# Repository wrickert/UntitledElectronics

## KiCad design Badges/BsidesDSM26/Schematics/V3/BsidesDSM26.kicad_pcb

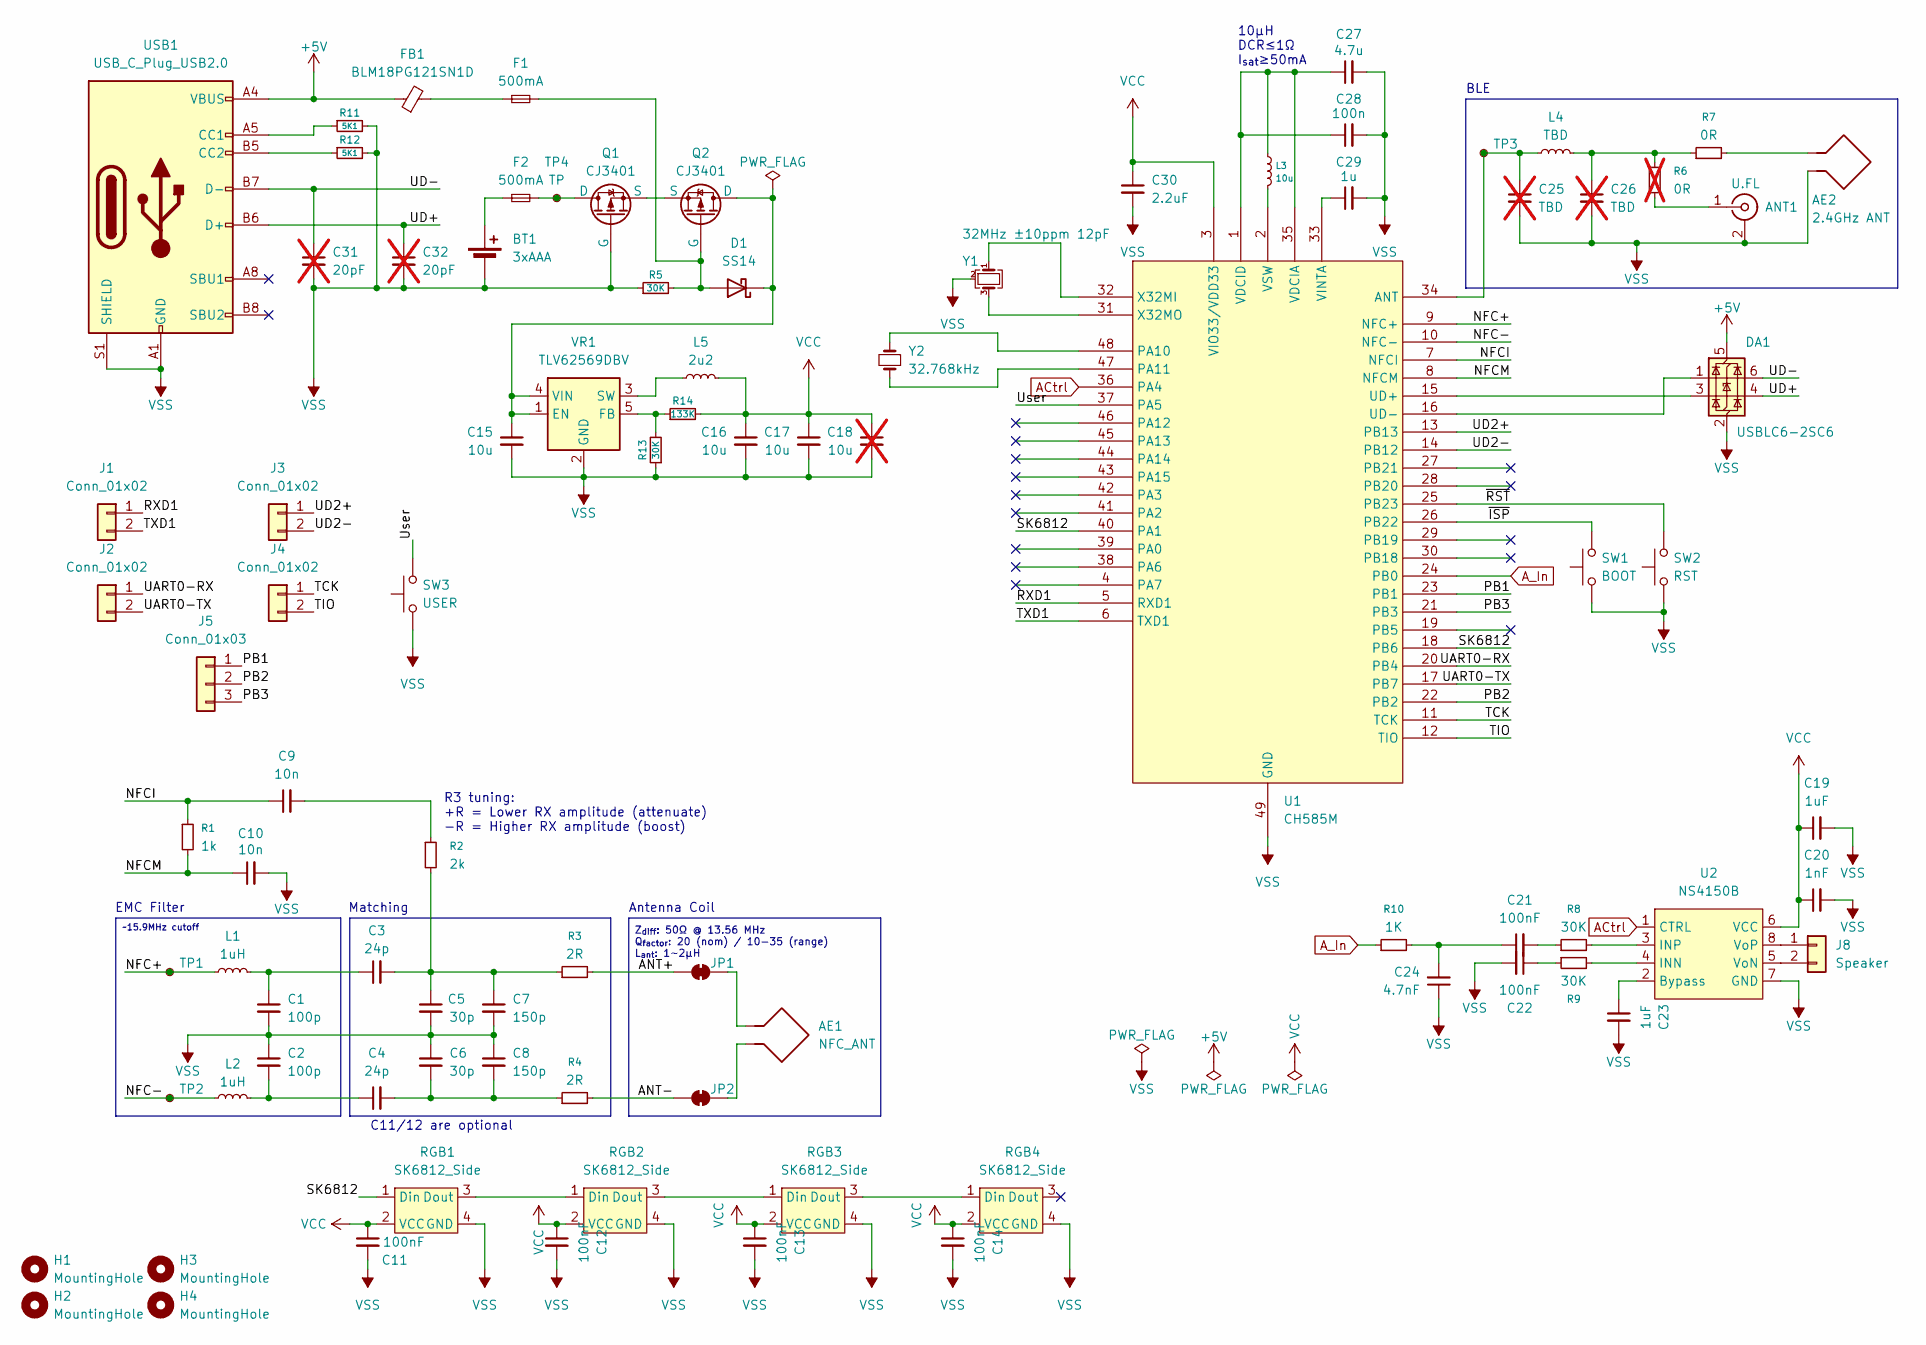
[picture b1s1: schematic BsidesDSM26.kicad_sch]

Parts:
AE1: NFC_ANT; NFC Anenna
AE2: 2.4GHz ANT; Texas_SWRA117D_2.4GHz_Left
ANT1: U.FL; U.FL_Hirose_U.FL-R-SMT-1_Vertical
BT1: 3xAAA; Keystone_5226_3AAA
C1, C2: 100p; C_0603_1608Metric
C3, C4: 24p; C_0603_1608Metric
C5, C6: 30p; C_0603_1608Metric
C7, C8: 150p; C_0603_1608Metric
C9, C10: 10n; C_0603_1608Metric
C11, C12, C13, C14, C21, C22: 100nF; C_0805_2012Metric
C15, C16, C17: 10u; C_0603_1608Metric; LCSC C3039688
C18: 10u; C_0603_1608Metric; LCSC C3039688; not fitted
C19: 1uF; C_0603_1608Metric
C20: 1nF; C_0603_1608Metric
C23: 1uF; C_0805_2012Metric
C24: 4.7nF; C_0805_2012Metric
C25, C26: TBD; C_0603_1608Metric; not fitted
C27: 4.7u; C_0603_1608Metric
C28: 100n; C_0805_2012Metric
C29: 1u; C_0603_1608Metric
C30: 2.2uF; C_0603_1608Metric
C31, C32: 20pF; C_0402_1005Metric_Pad0.74x0.62mm_HandSolder; not fitted
D1: SS14; D_SMA; LCSC C2986110
DA1: USBLC6-2SC6; SOT-23-6
F1, F2: 500mA; Fuse_1206_3216Metric; LCSC C2680506
FB1: BLM18PG121SN1D; L_0603_1608Metric_Pad1.05x0.95mm_HandSolder; LCSC C14709
H1, H2, H3, H4: MountingHole; M3ThreadedStandoff
J1, J2, J3, J4: Conn_01x02; PinHeader_1x02_P1.00mm_Vertical
J5: Conn_01x03; PinHeader_1x03_P2.54mm_Vertical
J8: Speaker; Molex_PicoBlade_53261-0271_1x02-1MP_P1.25mm_Horizontal
JP1, JP2: SolderJumper_2_Bridged; SolderJumper-2_P1.3mm_Bridged_RoundedPad1.0x1.5mm
L1, L2: 1uH; L_0603_1608Metric
L3: 10u; L_1008_2520Metric
L4: TBD; L_0603_1608Metric
L5: 2u2; L_1008_2520Metric_Pad1.43x2.20mm_HandSolder; LCSC C206332
Q1, Q2: CJ3401; SOT-23; LCSC C13799
R1: 1k; R_0603_1608Metric
R2: 2k; R_0603_1608Metric
R3, R4: 2R; R_0603_1608Metric
R5, R8, R9: 30K; R_0805_2012Metric
R6: 0R; R_0603_1608Metric; not fitted
R7: 0R; R_0603_1608Metric
R10: 1K; R_0805_2012Metric
R11, R12: 5K1; R_0603_1608Metric
R13: 30K; R_0603_1608Metric
R14: 133K; R_0603_1608Metric
RGB1, RGB2, RGB3, RGB4: SK6812_Side; SK6812SIDE-A-RVS
SW1: BOOT; TS3315A
SW2: RST; TS3315A
SW3: USER; TS3315A
TP1, TP2, TP3: TestPoint_Small; TestPoint_Pad_D1.0mm
TP4: TP; TestPoint_Pad_D1.0mm
U1: CH585M; QFN-48-1EP_5x5mm_P0.35mm_EP3.7x3.7mm
U2: NS4150B; MSOP-8_3x3mm_P0.65mm
USB1: USB_C_Plug_USB2.0; USB_C_Receptical-Jing
VR1: TLV62569DBV; SOT-23-5; LCSC C141836
Y1: 32MHz ±10ppm 12pF; Crystal_SMD_3225-4Pin_3.2x2.5mm
Y2: 32.768kHz; Crystal_SMD_3215-2Pin_3.2x1.5mm

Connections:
+5V: DA1.5 (VBUS), FB1.1, USB1.A4 (VBUS), USB1.A9 (VBUS), USB1.B4 (VBUS), USB1.B9 (VBUS)
/ANT+: JP1.1 (A), R3.2
/ANT-: JP2.1 (A), R4.2
/NFC+: L1.1, TP1.1 (1_1), U1.9 (NFC+)
/NFC-: L2.1, TP2.1 (1_1), U1.10 (NFC-)
/NFCI: C9.1, R1.1, U1.7 (NFCI)
/NFCM: C10.1, R1.2, U1.8 (NFCM)
/PB1: J5.1, U1.23 (PB1)
/PB2: J5.2, U1.22 (PB2)
/PB3: J5.3, U1.21 (PB3)
/RXD1: J1.1, U1.5 (RXD1)
/SK6812: RGB1.1 (Din), U1.18 (PB6), U1.40 (PA1)
/TCK: J4.1, U1.11 (TCK)
/TIO: J4.2, U1.12 (TIO)
/TXD1: J1.2, U1.6 (TXD1)
/UART0-RX: J2.1, U1.20 (PB4)
/UART0-TX: J2.2, U1.17 (PB7)
/UD2+: J3.1, U1.13 (PB13)
/UD2-: J3.2, U1.14 (PB12)
/UD+: C32.1, DA1.4 (I/O2), USB1.A6 (D+), USB1.B6 (D+)
/UD-: C31.1, DA1.6 (I/O1), USB1.A7 (D-), USB1.B7 (D-)
/User: SW3.2, U1.37 (PA5)
/~ISP: SW1.2, U1.26 (PB22)
/~RST: SW2.2, U1.25 (PB23)
ACtrl: U1.36 (PA4), U2.1 (CTRL)
A_In: R10.1, U1.24 (PB0)
unnamed: AE2.1, R7.2
unnamed: ANT1.1 (In), R6.2
unnamed: BT1.1 (+), F2.1
unnamed: C1.1, C3.1, L1.2
unnamed: C2.2, C4.1, L2.2
unnamed: C3.2, C5.1, C7.1, R2.2, R3.1
unnamed: C4.2, C6.2, C8.2, R4.1
unnamed: C9.2, R2.1
unnamed: C21.1, C24.2, R10.2
unnamed: C21.2, R8.1
unnamed: C22.1, R9.1
unnamed: C26.1, L4.2, R6.1, R7.1
unnamed: D1.2 (A), F1.2, Q2.1 (G), R5.2
unnamed: C15.1, D1.1 (K), Q2.3 (D), VR1.1 (EN), VR1.4 (VIN)
unnamed: F1.1, FB1.2
unnamed: J8.1, U2.8 (VoP)
unnamed: J8.2, U2.5 (VoN)
unnamed: AE1.1, JP1.2 (B)
unnamed: AE1.2, JP2.2 (B)
unnamed: F2.2, Q1.3 (D), TP4.1 (1_1)
unnamed: Q1.2 (S), Q2.2 (S)
unnamed: RGB1.3 (Dout), RGB2.1 (Din)
unnamed: RGB2.3 (Dout), RGB3.1 (Din)
unnamed: RGB3.3 (Dout), RGB4.1 (Din)
unnamed: C25.1, L4.1, TP3.1 (1_1), U1.34 (ANT)
unnamed: U1.48 (PA10), Y2.2
unnamed: U1.47 (PA11), Y2.1
unnamed: DA1.1 (I/O1), U1.16 (UD-)
unnamed: DA1.3 (I/O2), U1.15 (UD+)
unnamed: C27.1, C28.1, L3.1, U1.1 (VDCID), U1.35 (VDCIA)
unnamed: C29.1, U1.33 (VINTA)
unnamed: L3.2, U1.2 (VSW)
unnamed: U1.32 (X32MI), Y1.1
unnamed: U1.31 (X32MO), Y1.3
unnamed: C23.1, U2.2 (Bypass)
unnamed: R9.2, U2.4 (INN)
unnamed: R8.2, U2.3 (INP)
unnamed: R11.1, USB1.A5 (CC1)
unnamed: R12.1, USB1.B5 (CC2)
unnamed: R13.2, R14.1, VR1.5 (FB)
unnamed: L5.1, VR1.3 (SW)
VCC: C11.1, C12.1, C13.1, C14.1, C16.1, C17.1, C18.1, C19.1, C20.1, C30.1, L5.2, R14.2, RGB1.2 (VCC), RGB2.2 (VCC), RGB3.2 (VCC), RGB4.2 (VCC), U1.3 (VIO33/VDD33), U2.6 (VCC)
VSS: AE2.2, ANT1.2 (Ext), BT1.2 (-), C1.2, C2.1, C5.2, C6.1, C7.2, C8.1, C10.2, C11.2, C12.2, C13.2, C14.2, C15.2, C16.2, C17.2, C18.2, C19.2, C20.2, C22.2, C23.2, C24.1, C25.2, C26.2, C27.2, C28.2, C29.2, C30.2, C31.2, C32.2, DA1.2 (GND), Q1.1 (G), R5.1, R11.2, R12.2, R13.1, RGB1.4 (GND), RGB2.4 (GND), RGB3.4 (GND), RGB4.4 (GND), SW1.1, SW2.1, SW3.1, U1.49 (GND), U2.7 (GND), USB1.A1 (GND), USB1.A12 (GND), USB1.B1 (GND), USB1.B12 (GND), USB1.S1 (SHIELD), VR1.2 (GND), Y1.2 (G), Y1.4 (G)

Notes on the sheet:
10µH DCR≤1Ω I_{sat}≥50mA
Antenna Coil
Matching
Z_{diff​}: 50Ω @ 13.56 MHz Q_{factor​}: 20 (nom) / 10-35 (range) L_{ant​}: 1∼2μH
BLE
C11/12 are optional
EMC Filter
~15.9MHz cutoff
R3 tuning: +R = Lower RX amplitude (attenuate) -R = Higher RX amplitude (boost)

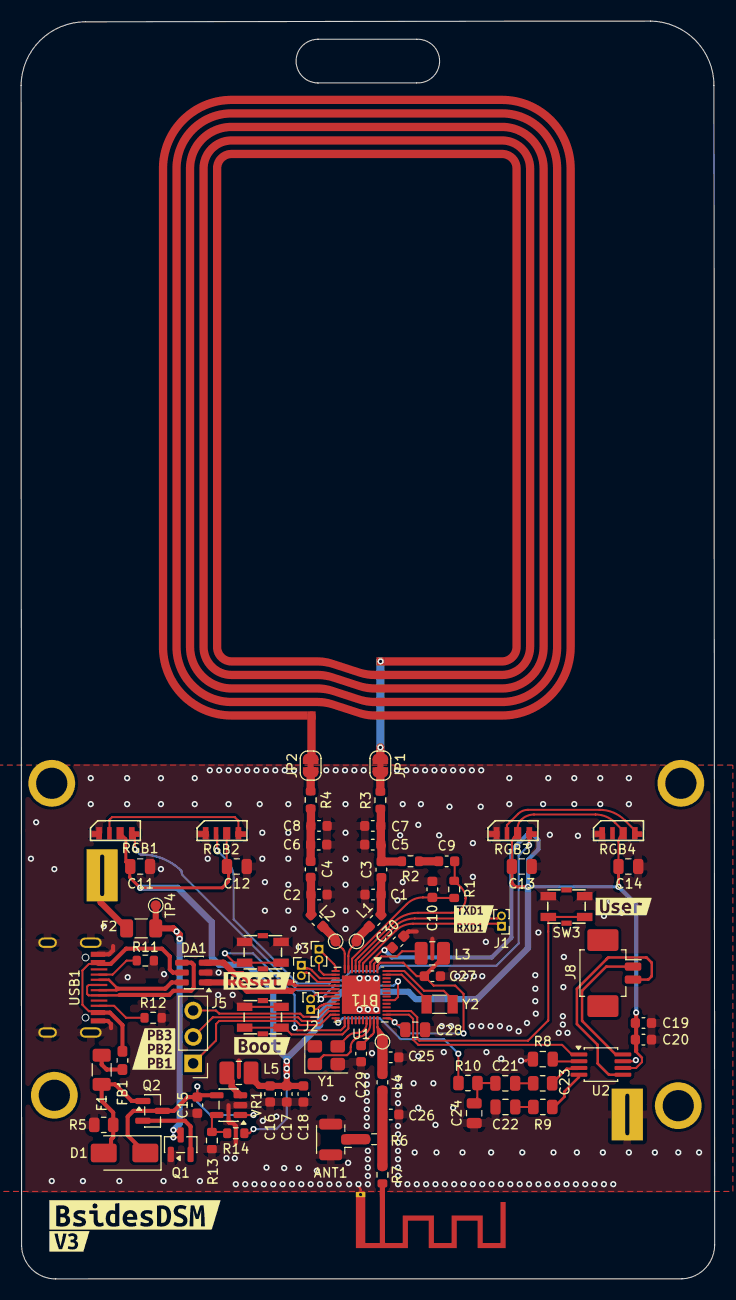
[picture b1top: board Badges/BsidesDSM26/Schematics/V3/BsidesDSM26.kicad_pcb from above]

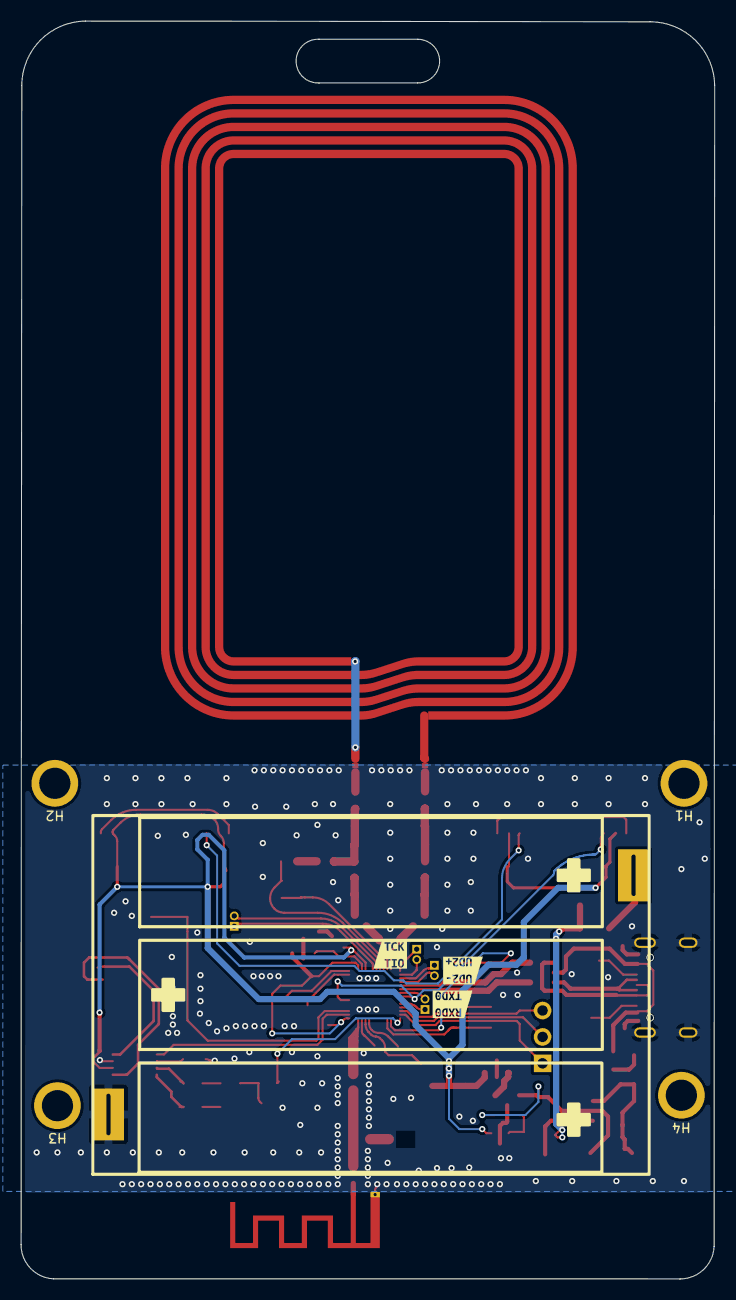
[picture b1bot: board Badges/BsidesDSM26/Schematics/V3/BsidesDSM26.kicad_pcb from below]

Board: 2 copper layers, 66.7 x 121.0 mm, 99 parts (7 on the bottom side), 69 nets.

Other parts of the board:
kibuzzard-6A035753: G***; kibuzzard-6A035753
kibuzzard-69CD6EDC: G***; kibuzzard-69CD6EDC
kibuzzard-69CD7A0E: G***; kibuzzard-69CD7A0E
kibuzzard-69CD7A3A: G***; kibuzzard-69CD7A3A
kibuzzard-69CD78FD: G***; kibuzzard-69CD78FD
kibuzzard-69CD79CB: G***; kibuzzard-69CD79CB
kibuzzard-69CD792A: G***; kibuzzard-69CD792A
kibuzzard-69CD7907: G***; kibuzzard-69CD7907
kibuzzard-69CD7919: G***; kibuzzard-69CD7919
kibuzzard-69FCE3C1: G***; kibuzzard-69FCE3C1

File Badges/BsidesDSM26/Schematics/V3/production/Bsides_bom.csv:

Designator,Footprint,Quantity,Value,LCSC Part #,Production
AE1,NFC Anenna,1,NFC_ANT,DNP,
AE2,Texas_SWRA117D_2.4GHz_Left,1,2.4GHz ANT,DNP,
ANT1,U.FL_Hirose_U.FL-R-SMT-1_Vertical,1,U.FL,DNP,
BT1,Keystone_5226_3AAA,1,3xAAA,DNP,
"C1, C2",603,2,100p,C576835,
"C10, C9",603,2,10n,C57112,
"C11, C12, C13, C14, C21, C22",805,6,100nF,C49678,
"C15, C16, C17, C18",603,4,10u,C3039688,
C19,603,1,1uF,C15849,
C20,603,1,1nF,C57112,
C23,805,1,1uF,C28323,
C24,805,1,4.7nF,C1779,
"C25, C26, L4",603,3,TBD,DNP,
C27,603,1,4.7u,C19666,
C28,805,1,100n,C49678,
C29,603,1,1u,C15849,
"C3, C4",603,2,24p,C107044,
C30,603,1,2.2uF,C23630,
"C31, C32",402,2,20pF,DNP,
"C5, C6",603,2,30p,C1658,
"C7, C8",603,2,150p,C22399613,
D1,D_SMA,1,SS14,C2986110,
DA1,SOT-23-6,1,USBLC6-2SC6,C7519,
"F1, F2",1206,2,500mA,C2680506,
FB1,603,1,BLM18PG121SN1D,C14709,
"J1, J2, J3, J4",PinHeader_1x02_P1.00mm_Vertical,4,Conn_01x02,DNP,
J5,PinHeader_1x03_P2.54mm_Vertical,1,Conn_01x03,DNP,
J8,Molex_PicoBlade_53261-0271_1x02-1MP_P1.25mm_Horizontal,1,Speaker,C7433453,
"L1, L2",603,2,1uH,C711163,
L3,1008,1,10u,C5289273 ,
L5,1008,1,2u2,C206332,
"Q1, Q2",SOT-23,2,CJ3401,C13799,
R1,603,1,1k,C21190,
R10,805,1,1K,C17513,
"R11, R12",603,2,5K1,C23186,
R13,603,1,30K,C22984,
R14,603,1,133K,C861659,
R2,603,1,2k,C22975,
"R3, R4",603,2,2R,C22977,
"R5, R8, R9",805,3,30K,C17621,
"R6, R7",603,2,0R,DNP,
"RGB1, RGB2, RGB3, RGB4",SK6812SIDE-A-RVS,4,SK6812_Side,C5378737,
SW1,TS3315A,1,BOOT,C2905041,
SW2,TS3315A,1,RST,C2905041,
SW3,TS3315A,1,USER,C2905041,
"TP1, TP2, TP3",TestPoint_Pad_D1.0mm,3,TestPoint_Small,DNP,
TP4,TestPoint_Pad_D1.0mm,1,TP,DNP,
U1,QFN-48-1EP_5x5mm_P0.35mm_EP3.7x3.7mm,1,CH585M,C42381469,
U2,MSOP-8_3x3mm_P0.65mm,1,NS4150B,C189961,
USB1,USB_C_Receptical-Jing,1,USB_C_Plug_USB2.0,C47345355,
VR1,SOT-23-5,1,TLV62569DBV,C141836,
Y1,Crystal_SMD_3225-4Pin_3.2x2.5mm,1,32MHz ±10ppm 12pF,C19723366,
Y2,Crystal_SMD_3215-2Pin_3.2x1.5mm,1,32.768kHz,C32346,

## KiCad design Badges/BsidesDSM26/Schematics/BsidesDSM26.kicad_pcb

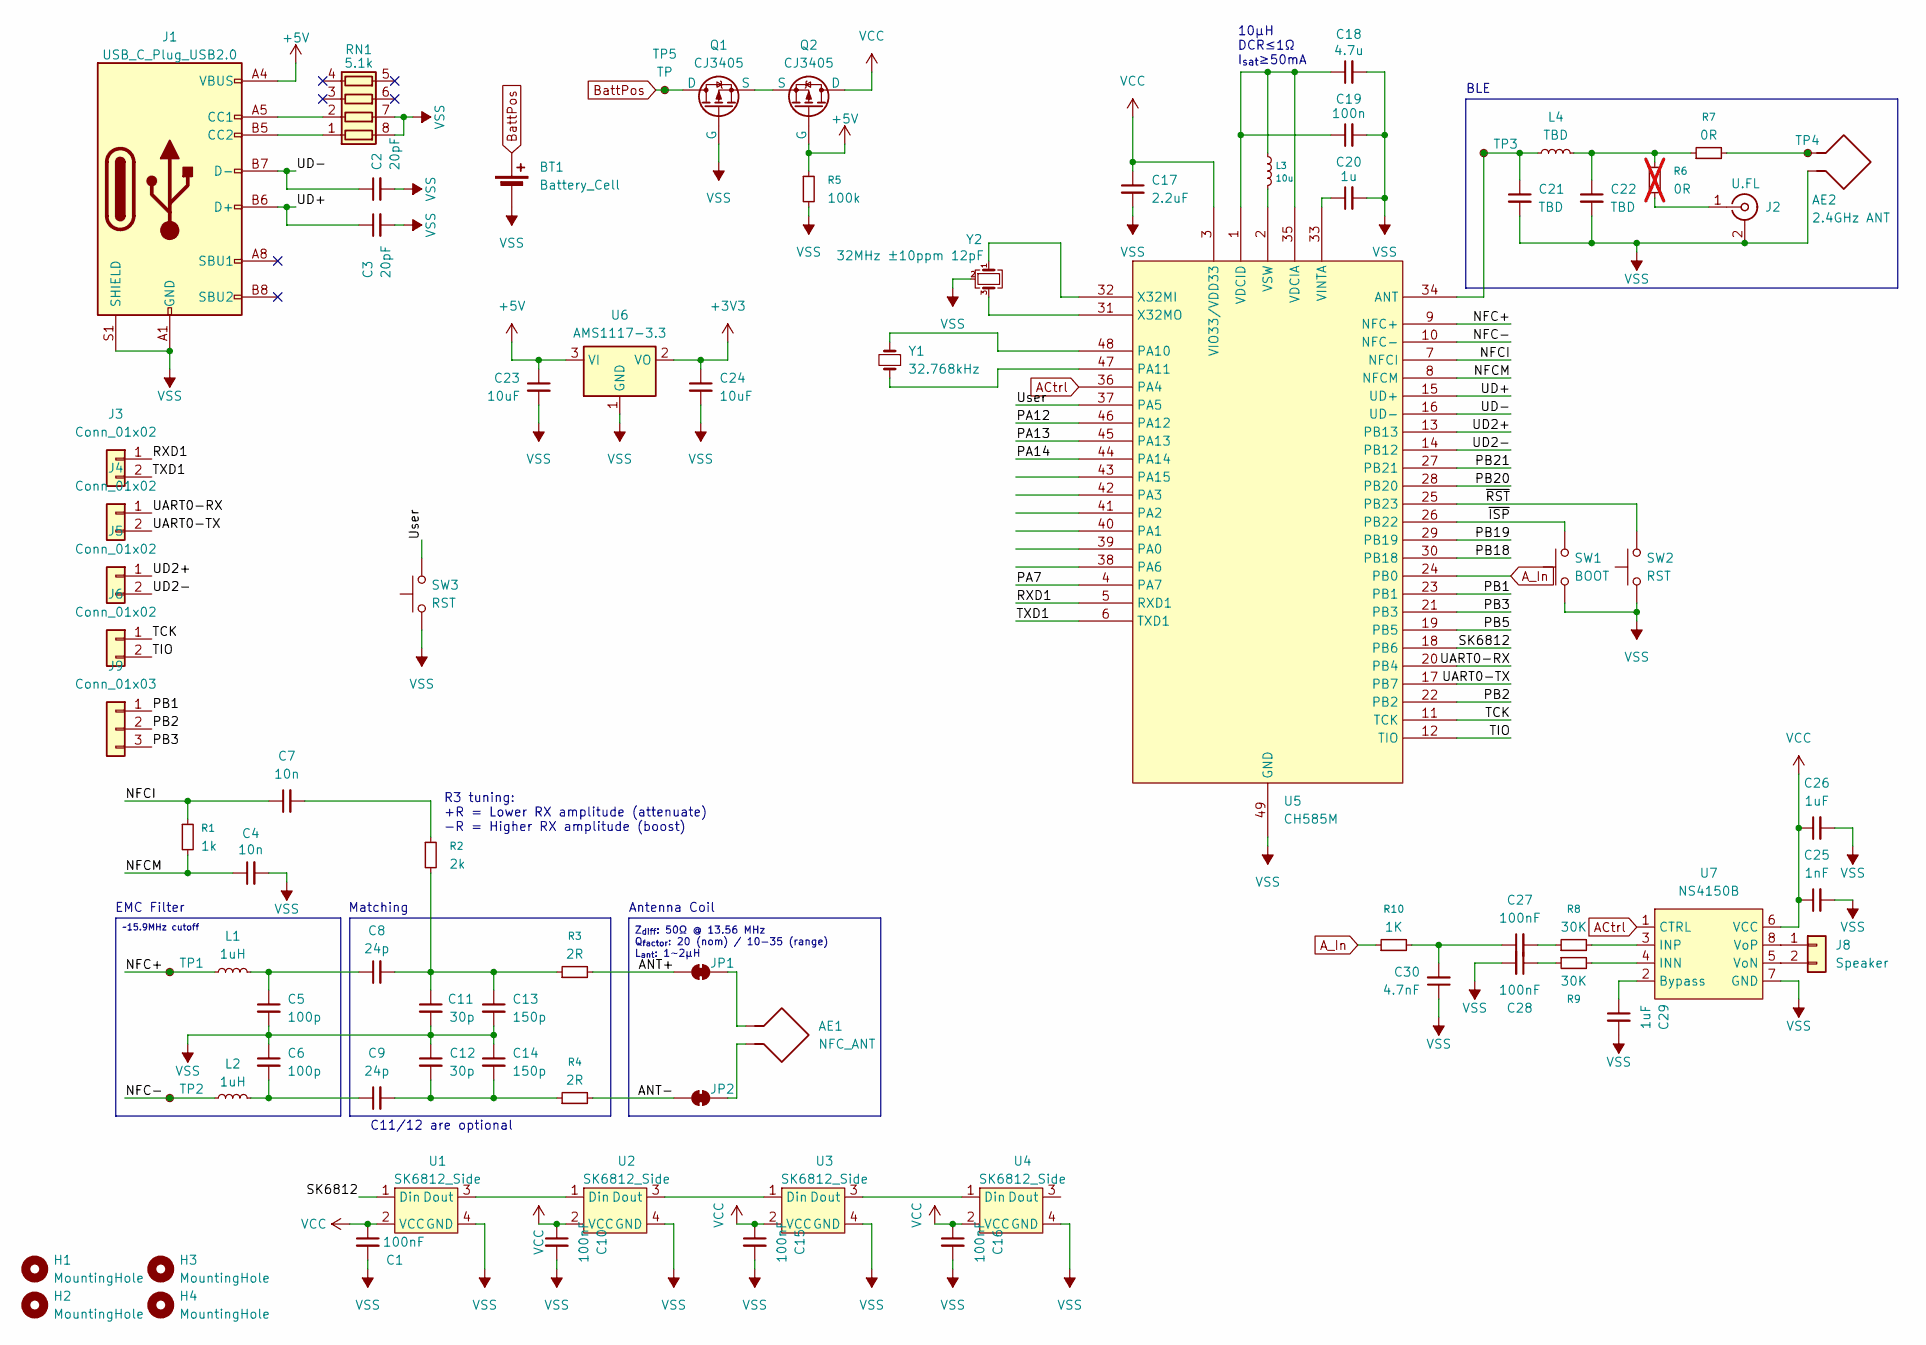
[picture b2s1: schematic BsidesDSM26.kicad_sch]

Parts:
AE1: NFC_ANT; NFC Anenna
AE2: 2.4GHz ANT; Texas_SWRA117D_2.4GHz_Left
BT1: Battery_Cell; Keystone5220_AA
C1, C10, C15, C16, C27, C28: 100nF; C_0805_2012Metric
C2, C3: 20pF; C_0805_2012Metric
C4, C7: 10n; C_0603_1608Metric
C5, C6: 100p; C_0603_1608Metric
C8, C9: 24p; C_0603_1608Metric
C11, C12: 30p; C_0603_1608Metric
C13, C14: 150p; C_0603_1608Metric
C17: 2.2uF; C_0805_2012Metric
C18: 4.7u; C_0805_2012Metric
C19: 100n; C_0603_1608Metric
C20: 1u; C_0603_1608Metric
C21, C22: TBD; C_0603_1608Metric
C23, C24: 10uF; C_0805_2012Metric
C25: 1nF; C_0805_2012Metric
C26, C29: 1uF; C_0805_2012Metric
C30: 4.7nF; C_0805_2012Metric
H1, H2, H3, H4: MountingHole; M3ThreadedStandoff
J1: USB_C_Plug_USB2.0; USB_C_Receptical-Jing
J2: U.FL; U.FL_Hirose_U.FL-R-SMT-1_Vertical
J3, J4, J5, J6: Conn_01x02; PinHeader_1x02_P1.00mm_Vertical
J8: Speaker; Molex_PicoBlade_53261-0271_1x02-1MP_P1.25mm_Horizontal
J9: Conn_01x03; PinHeader_1x03_P2.54mm_Vertical
JP1, JP2: SolderJumper_2_Bridged; SolderJumper-2_P1.3mm_Bridged_RoundedPad1.0x1.5mm
L1, L2: 1uH; L_0603_1608Metric
L3: 10u; L_1008_2520Metric
L4: TBD; L_0603_1608Metric
Q1, Q2: CJ3405; SOT-23
R1: 1k; R_0603_1608Metric
R2: 2k; R_0603_1608Metric
R3, R4: 2R; R_0603_1608Metric
R5: 100k; R_0805_2012Metric
R6: 0R; R_0603_1608Metric; not fitted
R7: 0R; R_0603_1608Metric
R8, R9: 30K; R_0805_2012Metric
R10: 1K; R_0805_2012Metric
RN1: 5.1k; R_Array_Convex_4x0603
SW1: BOOT; TS3315A
SW2, SW3: RST; TS3315A
TP1, TP2, TP3, TP4: TestPoint_Small; TestPoint_Pad_D1.0mm
TP5: TP; TestPoint_Pad_D1.0mm
U1, U2, U3, U4: SK6812_Side; SK6812SIDE-A-RVS
U5: CH585M; QFN-48-1EP_5x5mm_P0.35mm_EP3.7x3.7mm
U6: AMS1117-3.3; SOT-223-3_TabPin2
U7: NS4150B; MSOP-8_3x3mm_P0.65mm
Y1: 32.768kHz; Crystal_SMD_3215-2Pin_3.2x1.5mm
Y2: 32MHz ±10ppm 12pF; Crystal_SMD_3225-4Pin_3.2x2.5mm

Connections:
+5V: C23.1, J1.A4 (VBUS), J1.A9 (VBUS), J1.B4 (VBUS), J1.B9 (VBUS), Q2.1 (G), R5.1, U6.3 (VI)
/ANT+: JP1.1 (A), R3.2
/ANT-: JP2.1 (A), R4.2
/NFC+: L1.1, TP1.1, U5.9 (NFC+)
/NFC-: L2.1, TP2.1, U5.10 (NFC-)
/NFCI: C7.1, R1.1, U5.7 (NFCI)
/NFCM: C4.1, R1.2, U5.8 (NFCM)
/PA7: U5.4 (PA7)
/PA12: U5.46 (PA12)
/PA13: U5.45 (PA13)
/PA14: U5.44 (PA14)
/PB1: J9.1, U5.23 (PB1)
/PB2: J9.2, U5.22 (PB2)
/PB3: J9.3, U5.21 (PB3)
/PB5: U5.19 (PB5)
/PB18: U5.30 (PB18)
/PB19: U5.29 (PB19)
/PB20: U5.28 (PB20)
/PB21: U5.27 (PB21)
/RXD1: J3.1, U5.5 (RXD1)
/SK6812: U1.1 (Din), U5.18 (PB6)
/TCK: J6.1, U5.11 (TCK)
/TIO: J6.2, U5.12 (TIO)
/TXD1: J3.2, U5.6 (TXD1)
/UART0-RX: J4.1, U5.20 (PB4)
/UART0-TX: J4.2, U5.17 (PB7)
/UD2+: J5.1, U5.13 (PB13)
/UD2-: J5.2, U5.14 (PB12)
/UD+: C3.1, J1.A6 (D+), J1.B6 (D+), U5.15 (UD+)
/UD-: C2.1, J1.A7 (D-), J1.B7 (D-), U5.16 (UD-)
/User: SW3.2, U5.37 (PA5)
/~ISP: SW1.2, U5.26 (PB22)
/~RST: SW2.2, U5.25 (PB23)
ACtrl: U5.36 (PA4), U7.1 (CTRL)
A_In: R10.1, U5.24 (PB0)
BattPos: BT1.1 (+), Q1.3 (D), TP5.1
unnamed: AE2.1, R7.2, TP4.1
unnamed: C5.1, C8.1, L1.2
unnamed: C6.2, C9.1, L2.2
unnamed: C7.2, R2.1
unnamed: C8.2, C11.1, C13.1, R2.2, R3.1
unnamed: C9.2, C12.2, C14.2, R4.1
unnamed: C22.1, L4.2, R6.1, R7.1
unnamed: C27.1, C30.2, R10.2
unnamed: C27.2, R8.1
unnamed: C28.1, R9.1
unnamed: J1.A5 (CC1), RN1.2 (R2.1)
unnamed: J1.B5 (CC2), RN1.1 (R1.1)
unnamed: J2.1 (In), R6.2
unnamed: J8.1, U7.8 (VoP)
unnamed: J8.2, U7.5 (VoN)
unnamed: AE1.1, JP1.2 (B)
unnamed: AE1.2, JP2.2 (B)
unnamed: Q1.2 (S), Q2.2 (S)
unnamed: U1.3 (Dout), U2.1 (Din)
unnamed: U2.3 (Dout), U3.1 (Din)
unnamed: U3.3 (Dout), U4.1 (Din)
unnamed: C21.1, L4.1, TP3.1, U5.34 (ANT)
unnamed: U5.48 (PA10), Y1.2
unnamed: U5.47 (PA11), Y1.1
unnamed: C18.1, C19.1, L3.1, U5.1 (VDCID), U5.35 (VDCIA)
unnamed: C20.1, U5.33 (VINTA)
unnamed: L3.2, U5.2 (VSW)
unnamed: U5.32 (X32MI), Y2.1
unnamed: U5.31 (X32MO), Y2.3
unnamed: C29.1, U7.2 (Bypass)
unnamed: R9.2, U7.4 (INN)
unnamed: R8.2, U7.3 (INP)
VSS: AE2.2, BT1.2 (-), C1.2, C2.2, C3.2, C4.2, C5.2, C6.1, C10.2, C11.2, C12.1, C13.2, C14.1, C15.2, C16.2, C17.2, C18.2, C19.2, C20.2, C21.2, C22.2, C23.2, C24.2, C25.2, C26.2, C28.2, C29.2, C30.1, J1.A1 (GND), J1.A12 (GND), J1.B1 (GND), J1.B12 (GND), J1.S1 (SHIELD), J2.2 (Ext), Q1.1 (G), R5.2, RN1.7 (R2.2), RN1.8 (R1.2), SW1.1, SW2.1, SW3.1, U1.4 (GND), U2.4 (GND), U3.4 (GND), U4.4 (GND), U5.49 (GND), U6.1 (GND), U7.7 (GND), Y2.2 (G), Y2.4 (G)

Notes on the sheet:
10µH DCR≤1Ω I_{sat}≥50mA
Antenna Coil
Matching
Z_{diff​}: 50Ω @ 13.56 MHz Q_{factor​}: 20 (nom) / 10-35 (range) L_{ant​}: 1∼2μH
BLE
C11/12 are optional
EMC Filter
~15.9MHz cutoff
R3 tuning: +R = Lower RX amplitude (attenuate) -R = Higher RX amplitude (boost)

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
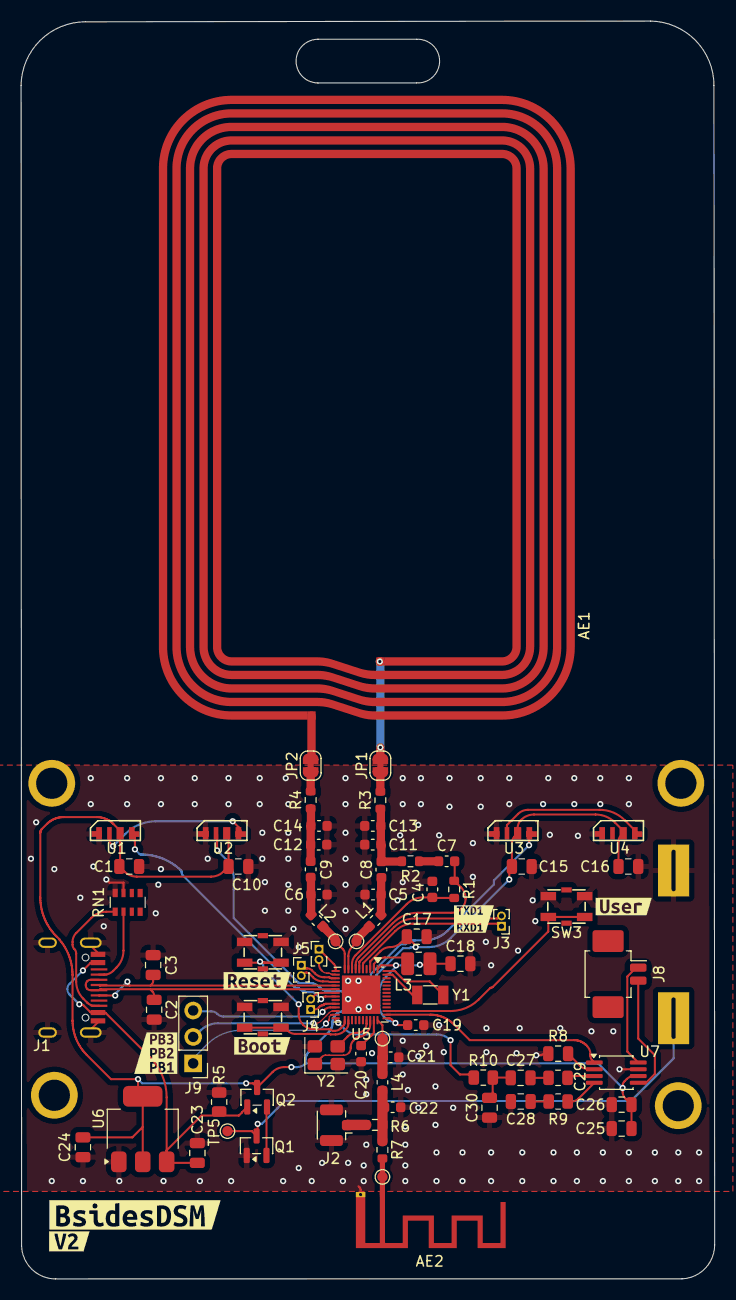
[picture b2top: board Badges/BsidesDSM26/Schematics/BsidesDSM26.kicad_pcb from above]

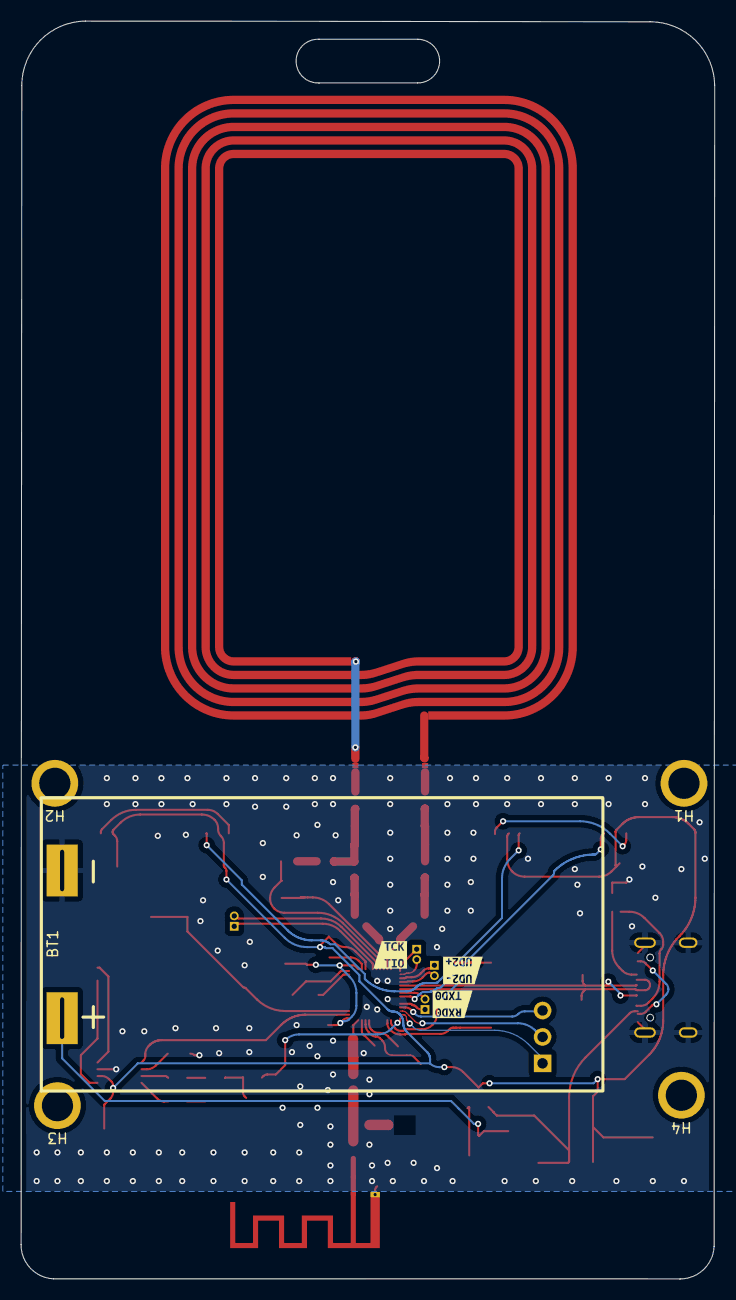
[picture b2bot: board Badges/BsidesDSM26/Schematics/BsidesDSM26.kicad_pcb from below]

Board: 2 copper layers, 66.7 x 121.0 mm, 91 parts (8 on the bottom side), 61 nets.

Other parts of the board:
kibuzzard-69CD6EDC: G***; kibuzzard-69CD6EDC
kibuzzard-69CD7A0E: G***; kibuzzard-69CD7A0E
kibuzzard-69CD7A3A: G***; kibuzzard-69CD7A3A
kibuzzard-69CD78FD: G***; kibuzzard-69CD78FD
kibuzzard-69CD79CB: G***; kibuzzard-69CD79CB
kibuzzard-69CD792A: G***; kibuzzard-69CD792A
kibuzzard-69CD7907: G***; kibuzzard-69CD7907
kibuzzard-69CD7919: G***; kibuzzard-69CD7919
kibuzzard-69FCB6F3: G***; kibuzzard-69FCB6F3
kibuzzard-69FCE3C1: G***; kibuzzard-69FCE3C1

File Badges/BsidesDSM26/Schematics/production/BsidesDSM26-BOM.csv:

Designator,Footprint,Quantity,Value,LCSC Part #
AE1,NFC Anenna,1,NFC_ANT,
AE2,Texas_SWRA117D_2.4GHz_Left,1,2.4GHz ANT,
BT1,PinHeader_1x02_P2.54mm_Vertical,1,Battery_Cell,
BZ1,Buzzer_CUI_CPT-9019S-SMT,1,Buzzer,
"C1, C10, C15, C16",0805,4,100nF,
"C11, C12",0603,2,30p,
"C13, C14",0603,2,150p,
C17,0805,1,2.2u,
C18,0805,1,4.7u,
C19,0603,1,100n,
"C2, C3",0805,2,20pF,
"C20, L1, L2",0603,3,1u,
"C21, C22, L4",0603,3,TBD,
"C23, C24",0805,2,C_Small,
"C4, C7",0603,2,10n,
"C5, C6",0603,2,100p,
"C8, C9",0603,2,24p,
D1,0805,1,D_Schottky,
"D2, D3, D4, D5",LED_Kingbright_APFA3010_3x1.5mm_Horizontal,4,APFA3010,
J1,USB_C_Receptical-Jing,1,USB_C_Plug_USB2.0,
J2,U.FL_Hirose_U.FL-R-SMT-1_Vertical,1,U.FL,
"J3, J4, J5, J6",PinHeader_1x02_P1.00mm_Vertical,4,Conn_01x02,
J7,PinHeader_1x04_P2.54mm_Vertical,1,Conn_01x04,
L3,0805,1,10u,
"Q1, Q2",SOT-23,2,PMOS,
R1,0603,1,1k,
R2,0603,1,2k,
"R3, R4",0603,2,2R,
R5,0805,1,100k,
"R6, R7",0603,2,0R,
RN1,R_Array_Convex_4x0603,1,5.1k,
"RN2, RN3",R_Array_Convex_4x0603,2,R_Pack04,
SW1,TS3315A,1,BOOT,
"SW2, SW3",TS3315A,2,RST,
"TP1, TP2, TP3, TP4",TestPoint_Pad_D1.0mm,4,TestPoint_Small,
"U1, U2, U3, U4",SK6812SIDE-A-RVS,4,SK6812_Side,
U5,QFN-48-1EP_5x5mm_P0.35mm_EP3.7x3.7mm,1,CH585M,
U6,SOT-223-3_TabPin2,1,AMS1117-3.3,
Y1,Crystal_SMD_3215-2Pin_3.2x1.5mm,1,32.768kHz,
Y2,Crystal_SMD_3225-4Pin_3.2x2.5mm,1,32MHz ±10ppm 12pF,
